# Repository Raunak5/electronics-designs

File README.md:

# KiCad Projects

This repository contains my KiCad practice projects and electronic circuit designs.

Projects:

- Transformerless Power Supply
- AC to DC Converter
- Simple Voltage Regulator

Tools Used:

- KiCad
- Git
- GitHub

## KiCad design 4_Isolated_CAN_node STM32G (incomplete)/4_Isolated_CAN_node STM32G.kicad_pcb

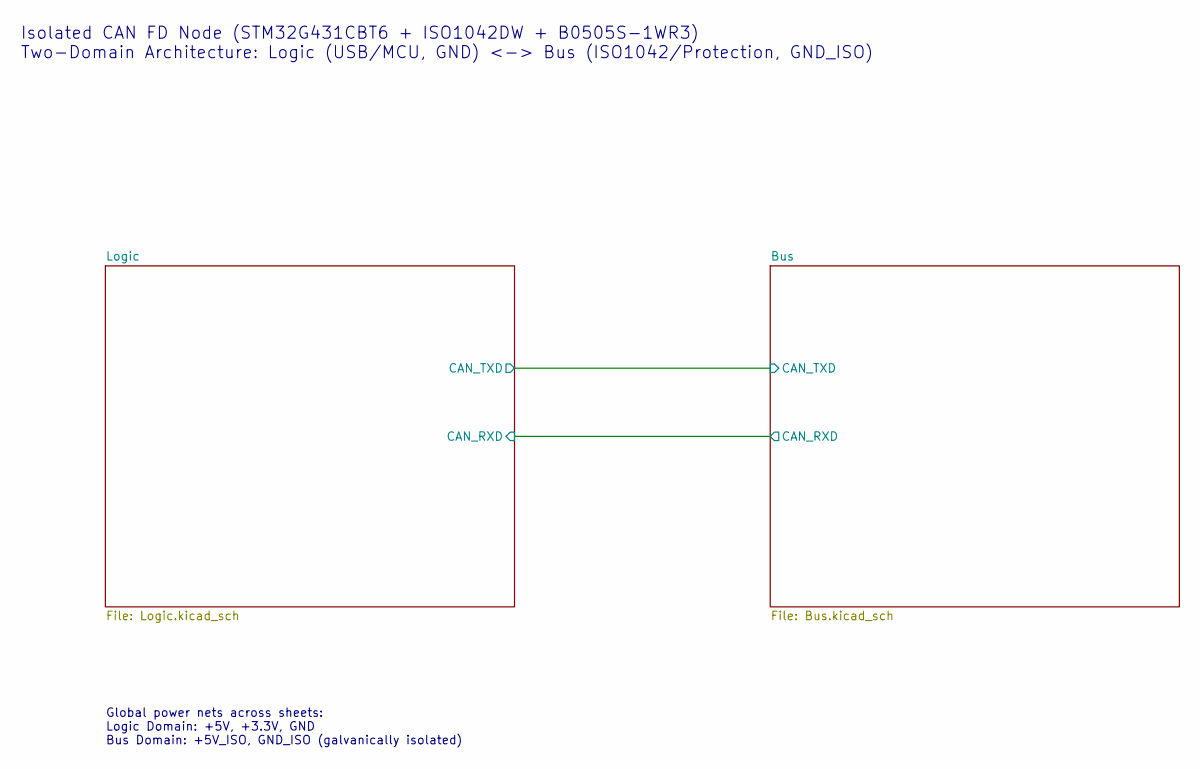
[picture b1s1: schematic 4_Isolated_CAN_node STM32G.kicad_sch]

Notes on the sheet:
Isolated CAN FD Node (STM32G431CBT6 + ISO1042DW + B0505S-1WR3) Two-Domain Architecture: Logic (USB/MCU, GND) <-> Bus (ISO1042/Protection, GND_ISO)
Global power nets across sheets: Logic Domain: +5V, +3.3V, GND Bus Domain: +5V_ISO, GND_ISO (galvanically isolated)

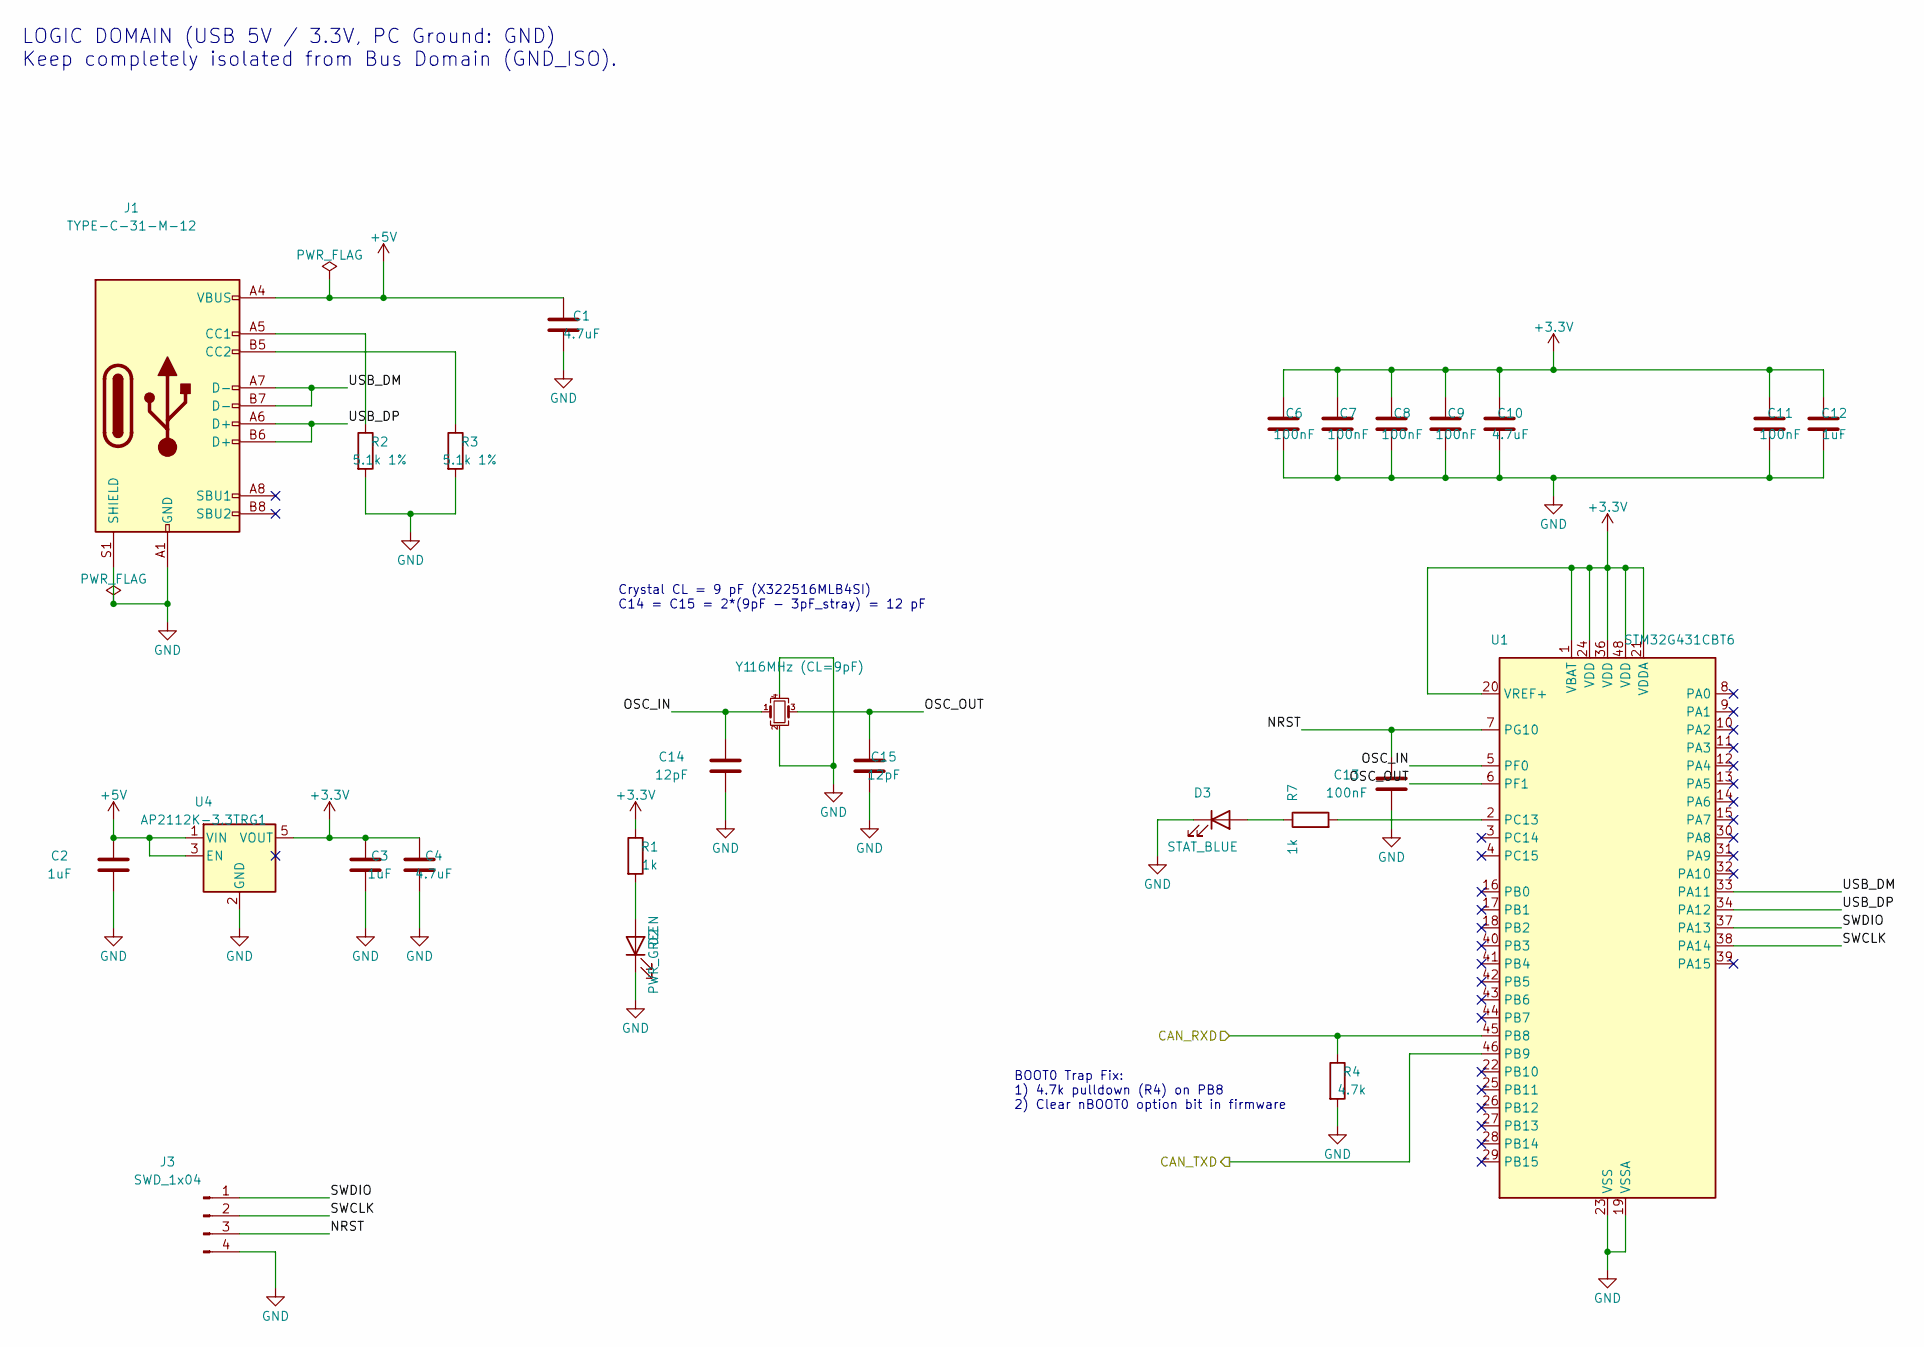
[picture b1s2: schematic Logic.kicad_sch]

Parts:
C1, C4, C10: 4.7uF; C_0603_1608Metric
C2, C3, C12: 1uF; C_0603_1608Metric
C6, C7, C8, C9, C11, C13: 100nF; C_0603_1608Metric
C14, C15: 12pF; C_0603_1608Metric
D2: PWR_GREEN; LED_0603_1608Metric
D3: STAT_BLUE; LED_0603_1608Metric
J1: TYPE-C-31-M-12; USB_C_Receptacle_HRO_TYPE-C-31-M-12; LCSC C165948
J3: SWD_1x04; PinHeader_1x04_P2.54mm_Vertical
R1, R7: 1k; R_0603_1608Metric
R2, R3: 5.1k 1%; R_0603_1608Metric
R4: 4.7k; R_0603_1608Metric
U1: STM32G431CBT6; LQFP-48_7x7mm_P0.5mm
U4: AP2112K-3.3TRG1; SOT-23-5; LCSC C51118
Y1: 16MHz (CL=9pF); Crystal_SMD_3225-4Pin_3.2x2.5mm; LCSC C13738

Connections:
+3.3V: C3.1, C4.1, C6.1, C7.1, C8.1, C9.1, C10.1, C11.1, C12.1, R1.1, U1.1 (VBAT), U1.20 (VREF+), U1.21 (VDDA), U1.24 (VDD), U1.36 (VDD), U1.48 (VDD), U4.5 (VOUT); also elsewhere on the board
+5V: C1.1, C2.1, J1.A4 (VBUS), J1.A9 (VBUS), J1.B4 (VBUS), J1.B9 (VBUS), U4.1 (VIN), U4.3 (EN); also elsewhere on the board
/Bus/CAN_RXD: R4.1, U1.45 (PB8); also elsewhere on the board
/Bus/CAN_TXD: U1.46 (PB9); also elsewhere on the board
/Logic/NRST: C13.1, J3.3, U1.7 (PG10)
/Logic/OSC_IN: C14.1, U1.5 (PF0), Y1.1
/Logic/OSC_OUT: C15.1, U1.6 (PF1), Y1.3
/Logic/SWCLK: J3.2, U1.38 (PA14)
/Logic/SWDIO: J3.1, U1.37 (PA13)
/Logic/USB_DM: J1.A7 (D-), J1.B7 (D-), U1.33 (PA11)
/Logic/USB_DP: J1.A6 (D+), J1.B6 (D+), U1.34 (PA12)
GND: C1.2, C2.2, C3.2, C4.2, C6.2, C7.2, C8.2, C9.2, C10.2, C11.2, C12.2, C13.2, C14.2, C15.2, D2.1 (K), D3.1 (K), J1.A1 (GND), J1.A12 (GND), J1.B1 (GND), J1.B12 (GND), J1.S1 (SHIELD), J3.4, R2.2, R3.2, R4.2, U1.19 (VSSA), U1.23 (VSS), U1.35 (VSS), U1.47 (VSS), U4.2 (GND), Y1.2, Y1.4; also elsewhere on the board
unnamed: D2.2 (A), R1.2
unnamed: D3.2 (A), R7.1
unnamed: J1.A5 (CC1), R2.1
unnamed: J1.B5 (CC2), R3.1
unnamed: R7.2, U1.2 (PC13)

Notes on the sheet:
LOGIC DOMAIN (USB 5V / 3.3V, PC Ground: GND) Keep completely isolated from Bus Domain (GND_ISO).
Crystal CL = 9 pF (X322516MLB4SI) C14 = C15 = 2*(9pF - 3pF_stray) = 12 pF
BOOT0 Trap Fix: 1) 4.7k pulldown (R4) on PB8 2) Clear nBOOT0 option bit in firmware

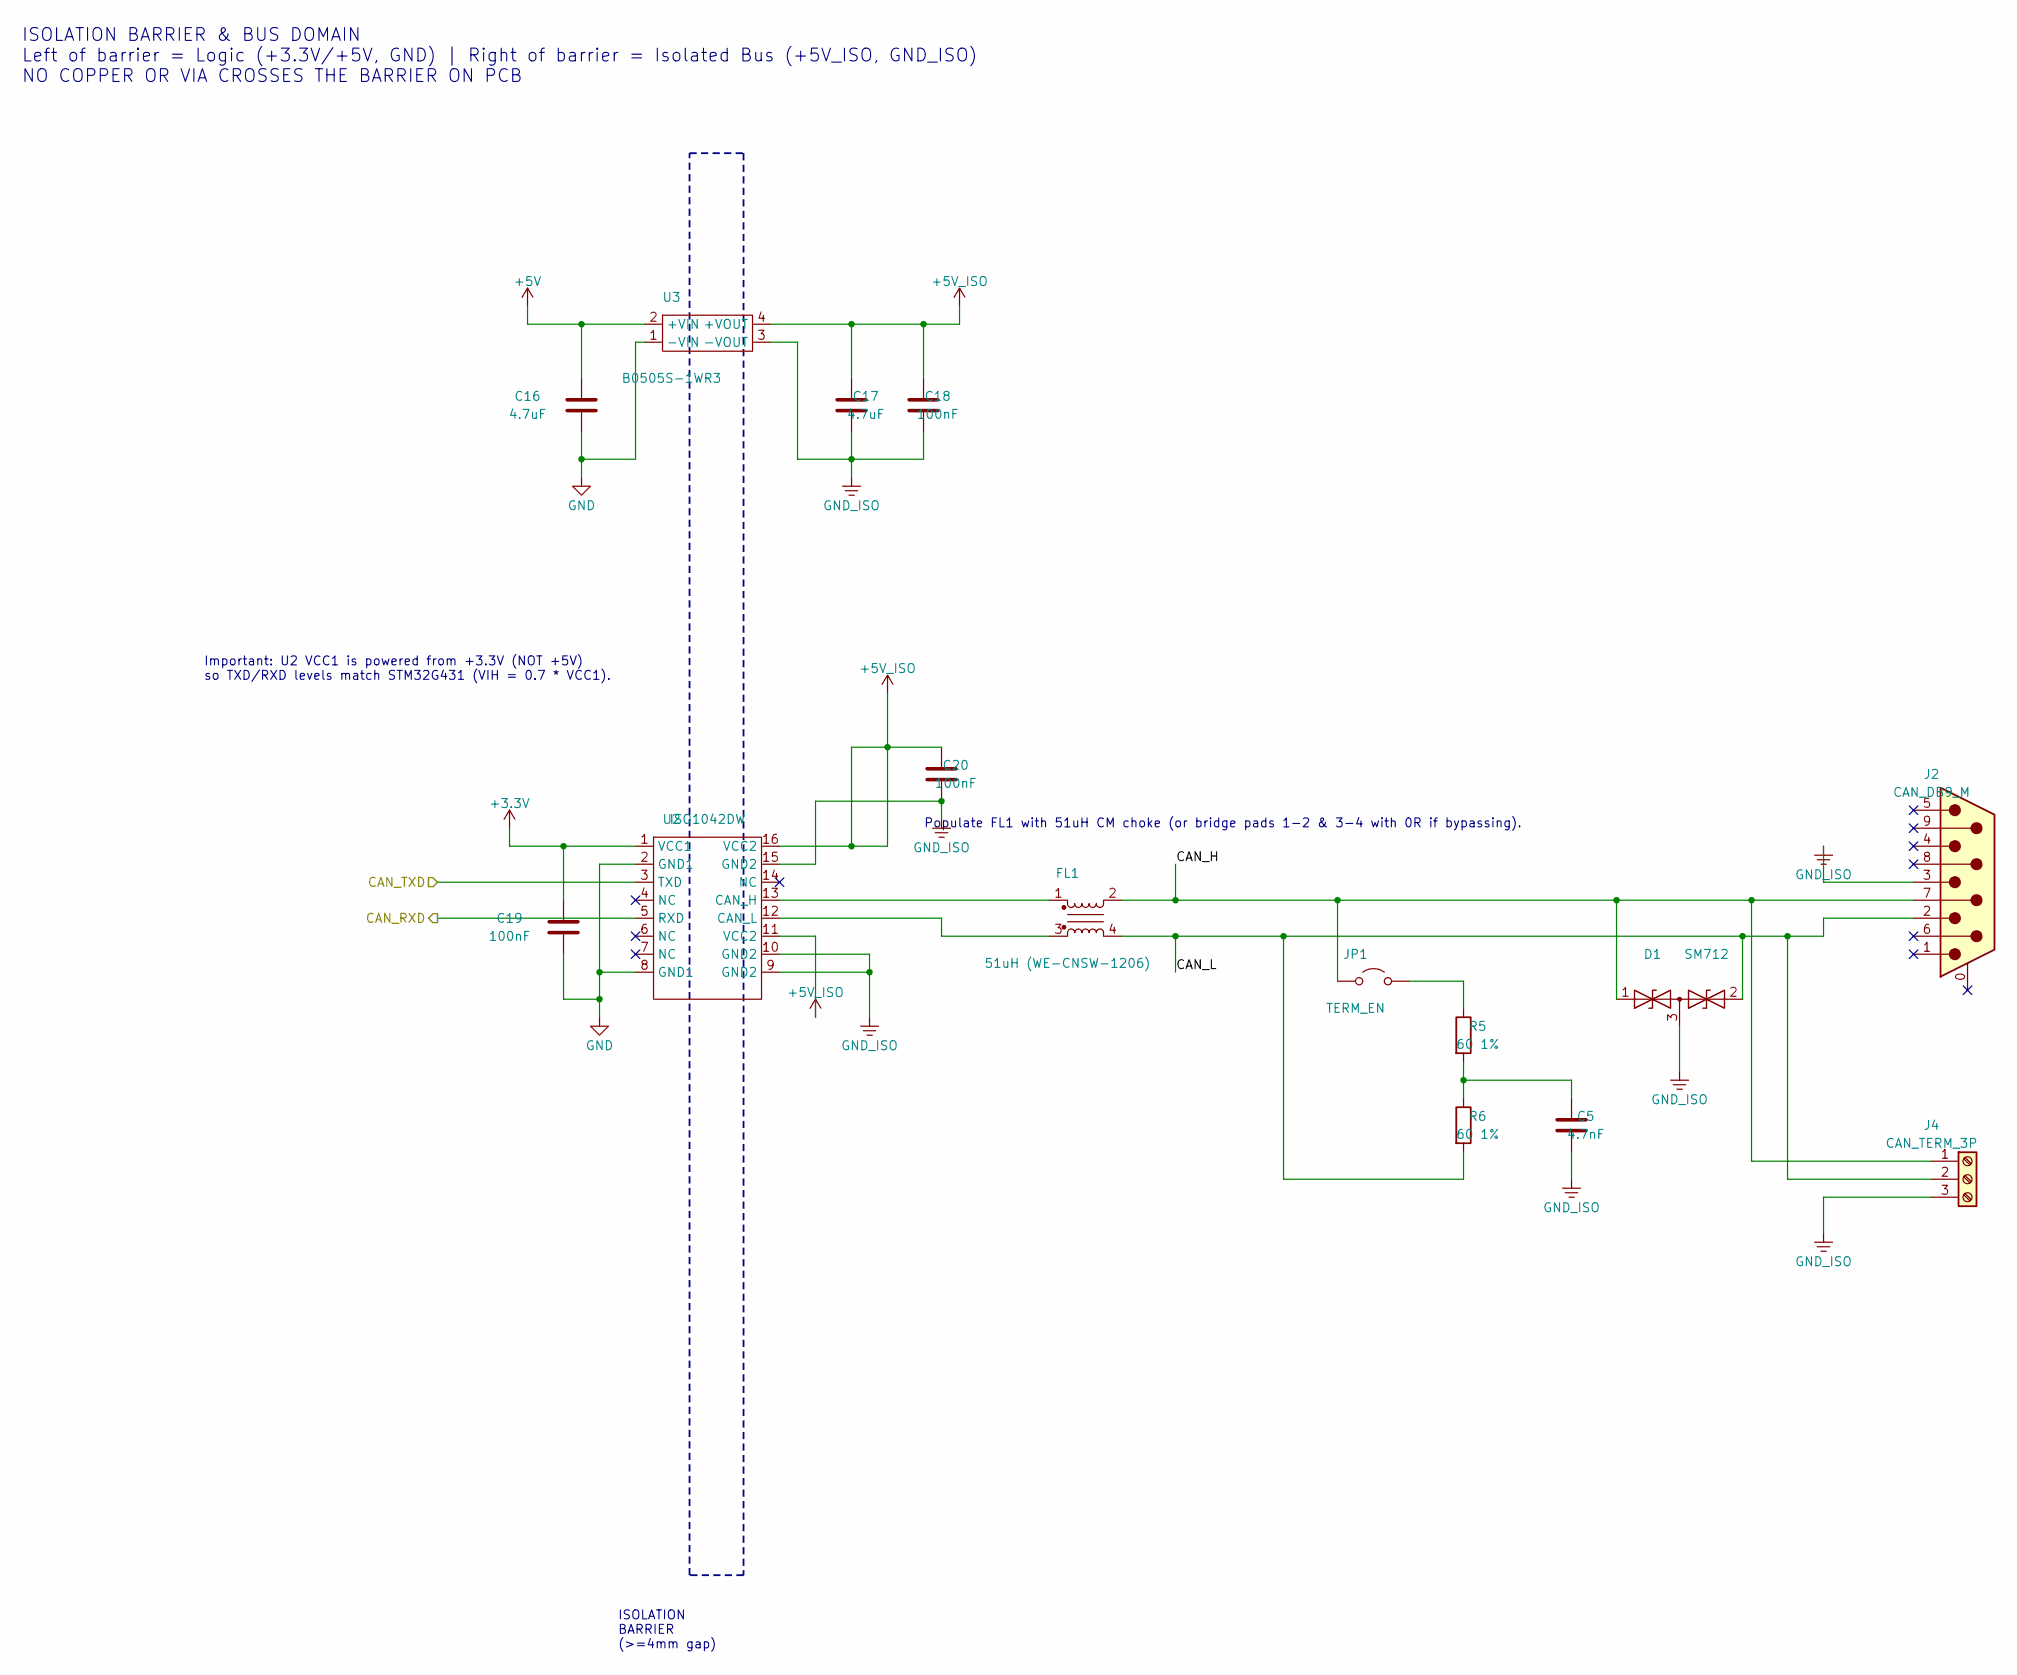
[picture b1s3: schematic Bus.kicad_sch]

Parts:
C5: 4.7nF; C_0603_1608Metric
C16, C17: 4.7uF; C_0603_1608Metric
C18, C19, C20: 100nF; C_0603_1608Metric
D1: SM712; SOT-23; LCSC C404012
FL1: 51uH (WE-CNSW-1206); L_CommonMode_Wurth_WE-CNSW-1206
J2: CAN_DB9_M; DSUB-9_Pins_Horizontal_P2.77x2.84mm_EdgePinOffset7.70mm_Hou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
J4: CAN_TERM_3P; TerminalBlock_Phoenix_MKDS-1,5-3-5.08_1x03_P5.08mm_Horizont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
JP1: TERM_EN; PinHeader_1x02_P2.54mm_Vertical
R5, R6: 60 1%; R_0603_1608Metric
U2: ISO1042DW; SOIC-16W_7.5x10.3mm_P1.27mm; LCSC C1848126
U3: B0505S-1WR3; Converter_DCDC_Murata_MEE1SxxxxSC_THT; LCSC C84643

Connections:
+3.3V: C19.1, U2.1 (VCC1); also elsewhere on the board
+5V: C16.1, U3.2 (+VIN); also elsewhere on the board
+5V_ISO: C17.1, C18.1, C20.1, U2.11 (VCC2), U2.16 (VCC2), U3.4 (+VOUT)
/Bus/CAN_H: D1.1 (A1), FL1.2, J2.7, J4.1, JP1.1 (A)
/Bus/CAN_L: D1.2 (A2), FL1.4, J2.2, J4.2, R6.2
/Bus/CAN_RXD: U2.5 (RXD); also elsewhere on the board
/Bus/CAN_TXD: U2.3 (TXD); also elsewhere on the board
GND: C16.2, C19.2, U2.2 (GND1), U2.8 (GND1), U3.1 (-VIN); also elsewhere on the board
GND_ISO: C5.2, C17.2, C18.2, C20.2, D1.3 (common), J2.3, J4.3, U2.9 (GND2), U2.10 (GND2), U2.15 (GND2), U3.3 (-VOUT)
unnamed: C5.1, R5.2, R6.1
unnamed: JP1.2 (B), R5.1
unnamed: FL1.1, U2.13 (CAN_H)
unnamed: FL1.3, U2.12 (CAN_L)

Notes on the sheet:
ISOLATION BARRIER & BUS DOMAIN Left of barrier = Logic (+3.3V/+5V, GND) | Right of barrier = Isolated Bus (+5V_ISO, GND_ISO) NO COPPER OR VIA CROSSES THE BARRIER ON PCB
ISOLATION BARRIER (>=4mm gap)
Important: U2 VCC1 is powered from +3.3V (NOT +5V) so TXD/RXD levels match STM32G431 (VIH = 0.7 * VCC1).
Populate FL1 with 51uH CM choke (or bridge pads 1-2 & 3-4 with 0R if bypassing).

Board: 2 copper layers, 41 parts (0 on the bottom side), 25 nets, no tracks yet.

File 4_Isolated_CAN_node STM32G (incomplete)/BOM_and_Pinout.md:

# Isolated CAN FD Node — Parts List (Phase 01) & Pinout Reference (Phase 02)

## Phase 01 — Locked BOM & LCSC Reference

> **Important Corrections Applied**
> - **U2 (`ISO1042DW` vs `ISO1042DWV`):** Your 16-pin wide-body SOIC footprint (`SOIC-16W_7.5x10.3mm_P1.27mm`) corresponds to TI's **16-pin `ISO1042DW` / `ISO1042DWR`**, not `ISO1042DWV` (which is an 8-pin wide-body SOIC). The schematic symbol and BOM use `ISO1042DW`.
> - **U2 Logic-Side Supply (`VCC1`):** `ISO1042` `VCC1` is wired to **`+3.3V`** (not `+5V`) because `VIH(min) = 0.7 × VCC1` (`2.31 V` at `3.3 V` vs `3.5 V` at `5 V`), matching the `3.3 V` STM32G431 I/O levels.
> - **Crystal Load Caps (`Y1`):** `X322516MLB4SI` (`C13738`) specifies `CL = 9 pF`. Assuming ~3 pF stray PCB/pin capacitance, `C14 = C15 = 2 × (9 pF − 3 pF) = 12 pF` (C0G/NP0).

| Ref | Part / Value | Package / Footprint | Verified LCSC / MPN Note | Qty (+Spares) |
| :--- | :--- | :--- | :--- | :--- |
| `U1` | `STM32G431CBT6` | `LQFP-48_7x7mm_P0.5mm` | ST `STM32G431CBT6` (check LCSC stock at order time) | 1 (+2 spares) |
| `U2` | `ISO1042DW` | `SOIC-16W_7.5x10.3mm_P1.27mm` | TI `ISO1042DWR` (`C1848126`) | 1 (+2 spares) |
| `U3` | `B0505S-1WR3` | `Converter_DCDC_Murata_MEE1SxxxxSC_THT` (SIP-4) | Mornsun `B0505S-1WR3` (`C84643` / alt `C2992394`) | 1 (+2 spares) |
| `U4` | `AP2112K-3.3TRG1` | `SOT-23-5` | Diodes Inc `AP2112K-3.3TRG1` (`C51118`) | 1 (+2 spares) |
| `Y1` | `16 MHz` crystal (`CL = 9 pF`) | `Crystal_SMD_3225-4Pin_3.2x2.5mm` | YXC `X322516MLB4SI` (`C13738`) | 1 (+2 spares) |
| `D1` | `SM712` (+12 V / −7 V TVS) | `SOT-23` | Bourns `CDSOT23-SM712` (`C404012`) | 1 (+2 spares) |
| `FL1` | `51 µH` CM choke (or `0 Ω` bypass) | `L_CommonMode_Wurth_WE-CNSW-1206` (1206-4) | Populate 1206-4 CAN CM choke later or bridge `1-2` & `3-4` with `0 Ω` | 1 |
| `J1` | USB-C 16-pin receptacle | `USB_C_Receptacle_HRO_TYPE-C-31-M-12` | HRO `TYPE-C-31-M-12` (`C165948`) | 1 |
| `J2` | DB9 male THT | `DSUB-9_Pins_Horizontal_P2.77x2.84mm_EdgePinOffset7.70mm_Housed_MountingHolesOffset9.12mm` | Standard right-angle PCB DE9 male | 1 |
| `J4` | 3-pin screw terminal (5.08 mm) | `TerminalBlock_Phoenix_MKDS-1,5-3-5.08_1x03_P5.08mm_Horizontal` | 3-pin 5.08 mm THT terminal block | 1 |
| `J3` | 4-pin SWD header | `PinHeader_1x04_P2.54mm_Vertical` | 1×4 2.54 mm header (`SWDIO`, `SWCLK`, `NRST`, `GND`) | 1 |
| `JP1` | 2-pin termination jumper | `PinHeader_1x02_P2.54mm_Vertical` | 1×2 2.54 mm header + shunt | 1 |
| `D2`, `D3` | Indicator LEDs (Power, Status) | `LED_0603_1608Metric` | Green (`D2`), Blue (`D3`) 0603 LEDs | 2 |
| `R1`, `R7` | `1 kΩ` (LED current limit) | `R_0603_1608Metric` | 0603 5% or 1% | 2 |
| `R2`, `R3` | `5.1 kΩ` 1% (USB-C CC1/CC2) | `R_0603_1608Metric` | 0603 1% | 2 |
| `R4` | `4.7 kΩ` (PB8/BOOT0 pulldown) | `R_0603_1608Metric` | 0603 1% or 5% | 1 |
| `R5`, `R6` | `60 Ω` 1% (split termination) | `R_0603_1608Metric` | 0603 1% (or `60.4 Ω` 1% E96 standard) | 2 |
| `C5` | `4.7 nF` (split termination) | `C_0603_1608Metric` | 0603 ≥50 V X7R/C0G | 1 |
| `C14`, `C15` | `12 pF` (HSE crystal load) | `C_0603_1608Metric` | 0603 C0G/NP0 50 V | 2 |
| `C6–C9, C11, C13, C18–C20` | `100 nF` (decoupling + NRST) | `C_0603_1608Metric` | 0603 X7R/X5R ≥16 V | 9 |
| `C2, C3, C12` | `1 µF` (LDO + VDDA) | `C_0603_1608Metric` | 0603 X5R/X7R ≥10 V | 3 |
| `C1, C4, C10, C16, C17` | `4.7 µF` (bulk decoupling) | `C_0603_1608Metric` | 0603 X5R/X7R ≥10 V | 5 |

---

## Phase 02 — STM32G431CBT6 Pinout & CubeMX Configuration

### CubeMX Setup Order
1. **SYS → Debug:** `Serial Wire` (`PA13` = `SWDIO`, `PA14` = `SWCLK`)
2. **RCC → HSE:** `Crystal/Ceramic Resonator` (`PF0` = `RCC_OSC_IN`, `PF1` = `RCC_OSC_OUT`, 16 MHz)
3. **USB → Device (FS):** Enabled (`PA11` = `USB_DM`, `PA12` = `USB_DP`)
4. **FDCAN1 → Mode:** `Classic + FD`, remapped off `PA11/PA12` onto **`PB8` (`FDCAN1_RX`)** and **`PB9` (`FDCAN1_TX`)**
5. **GPIO Output:** `PC13` = `LED_STATUS`
6. **Clock Tree:** 16 MHz HSE → PLL → `SYSCLK` (up to 170 MHz), **`48 MHz` USB clock** (via PLLQ or HSI48+CRS; use PLL from 16 MHz HSE for deterministic timing)
7. **Option Bytes (Critical for `PB8/BOOT0` trap):** Clear `nBOOT0` / `nSWBOOT0` (set `nSWBOOT0 = 0`, `nBOOT0 = 1` in STM32CubeProgrammer so MCU boots from main Flash regardless of `PB8` state; `R4` `4.7 kΩ` pulldown protects the pre-option-byte reset window).

### Pin Assignment Table (`U1: STM32G431CBT6`)

| Pin # | Pin Name | Schematic Net | Function |
| :--- | :--- | :--- | :--- |
| `1` | `VBAT` | `+3.3V` | Tied to 3.3 V + `100 nF` (`C6`) |
| `2` | `PC13` | `LED_STATUS` (via `R7`/`D3`) | Firmware status LED |
| `5` | `PF0` | `/Logic/OSC_IN` | 16 MHz HSE crystal (`Y1.1`, `C14` `12 pF`) |
| `6` | `PF1` | `/Logic/OSC_OUT` | 16 MHz HSE crystal (`Y1.3`, `C15` `12 pF`) |
| `7` | `PG10` | `/Logic/NRST` | Reset (`C13` `100 nF` to `GND`, `J3.3`) |
| `19` | `VSSA` | `GND` | Analog ground |
| `20` | `VREF+` | `+3.3V` | Analog reference (`C11`, `C12`) |
| `21` | `VDDA` | `+3.3V` | Analog power |
| `23, 35, 47` | `VSS` | `GND` | Logic ground |
| `24, 36, 48` | `VDD` | `+3.3V` | Logic power (`C7–C10`) |
| `33` | `PA11` | `/Logic/USB_DM` | USB FS D− (`J1.A7/B7`) |
| `34` | `PA12` | `/Logic/USB_DP` | USB FS D+ (`J1.A6/B6`) |
| `37` | `PA13` | `/Logic/SWDIO` | SWD data (`J3.1`) |
| `38` | `PA14` | `/Logic/SWCLK` | SWD clock (`J3.2`) |
| `45` | `PB8` | `/Bus/CAN_RXD` | `FDCAN1_RX` + `4.7 kΩ` (`R4`) to `GND` (`U2.RXD`) |
| `46` | `PB9` | `/Bus/CAN_TXD` | `FDCAN1_TX` (`U2.TXD`) |

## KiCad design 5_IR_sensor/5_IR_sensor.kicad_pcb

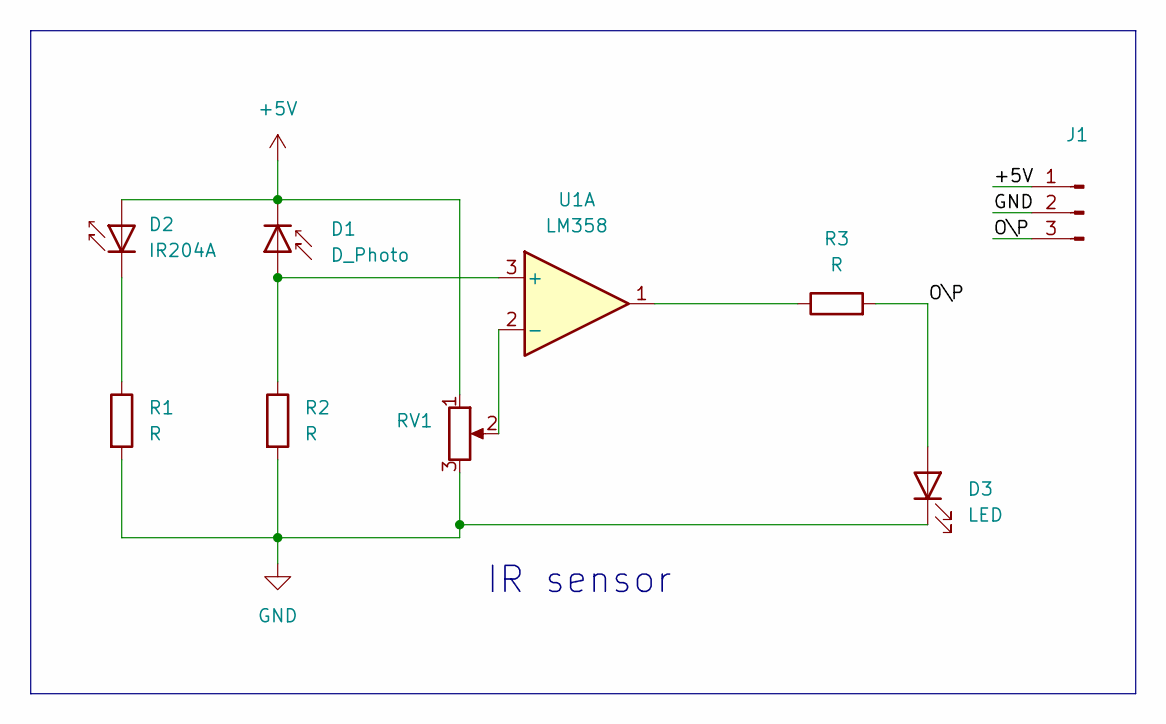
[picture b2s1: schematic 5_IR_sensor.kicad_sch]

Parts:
D1: D_Photo; LED_1W_3W_R8
D2: IR204A; LED_1W_3W_R8
D3: LED; LED_1W_3W_R8
J1: joint; PinHeader_1x03_P2.54mm_Vertical
R1, R2, R3: R; R_0805_2012Metric
RV1: R_Potentiometer; Potentiometer_ACP_CA9-VSMD_Vertical
U1: LM358; SOIC-8-1EP_3.9x4.9mm_P1.27mm_EP2.514x3.2mm_ThermalVias

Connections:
+5V: D1.1 (K), D2.2 (A), J1.1, RV1.1
/O\P: D3.2 (A), J1.3, R3.2
GND: D3.1 (K), J1.2, R1.2, R2.2, RV1.3
unnamed: D1.2 (A), R2.1, U1.3 (+)
unnamed: D2.1 (K), R1.1
unnamed: R3.1, U1.1
unnamed: RV1.2, U1.2 (-)

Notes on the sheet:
IR sensor

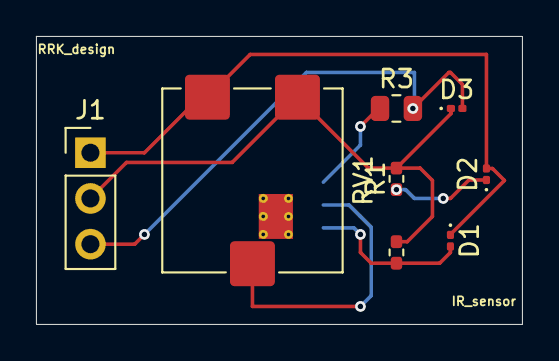
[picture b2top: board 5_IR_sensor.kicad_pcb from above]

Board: 2 copper layers, 27.0 x 16.0 mm, 9 parts (1 on the bottom side), 7 nets.

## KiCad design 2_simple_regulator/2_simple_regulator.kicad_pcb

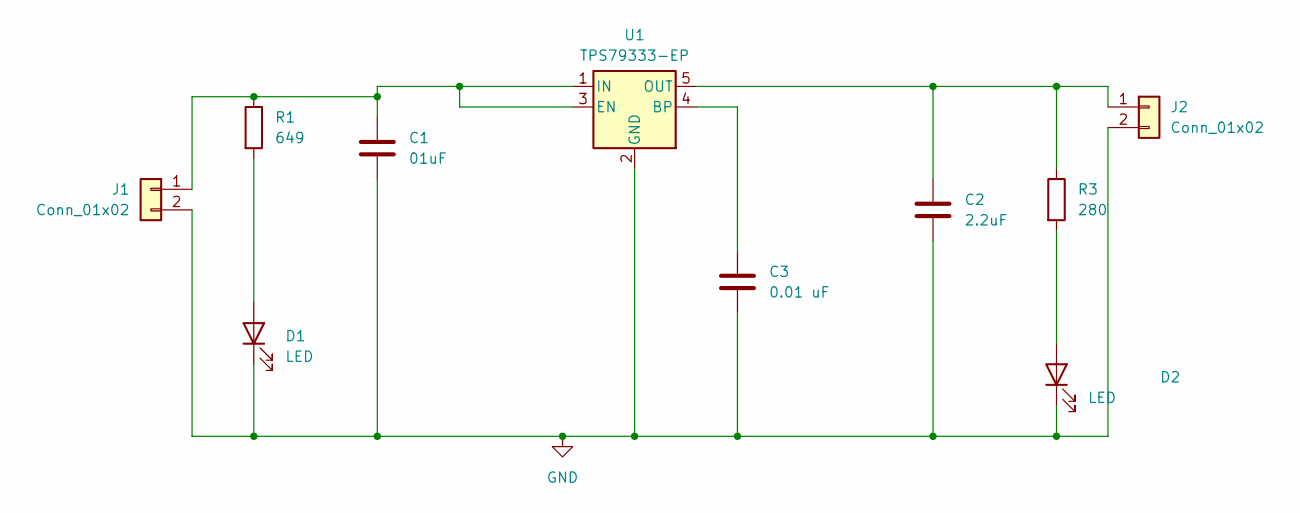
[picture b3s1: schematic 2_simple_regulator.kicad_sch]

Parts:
C1: 01uF; C_0805_2012Metric
C2: 2.2uF; C_0805_2012Metric
C3: 0.01 uF; C_0805_2012Metric
D1, D2: LED; LED_0805_2012Metric
J1, J2: Conn_01x02; PinHeader_1x02_P2.54mm_Vertical
R1: 649; R_0805_2012Metric
R3: 280; R_0805_2012Metric
U1: TPS79333-EP; SOT-23-5

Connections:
GND: C1.2, C2.2, C3.2, D1.1 (K), D2.1 (K), J1.2, J2.2, U1.2 (GND)
unnamed: D1.2 (A), R1.2
unnamed: D2.2 (A), R3.2
unnamed: C1.1, J1.1, R1.1, U1.1 (IN), U1.3 (EN)
unnamed: C2.1, J2.1, R3.1, U1.5 (OUT)
unnamed: C3.1, U1.4 (BP)

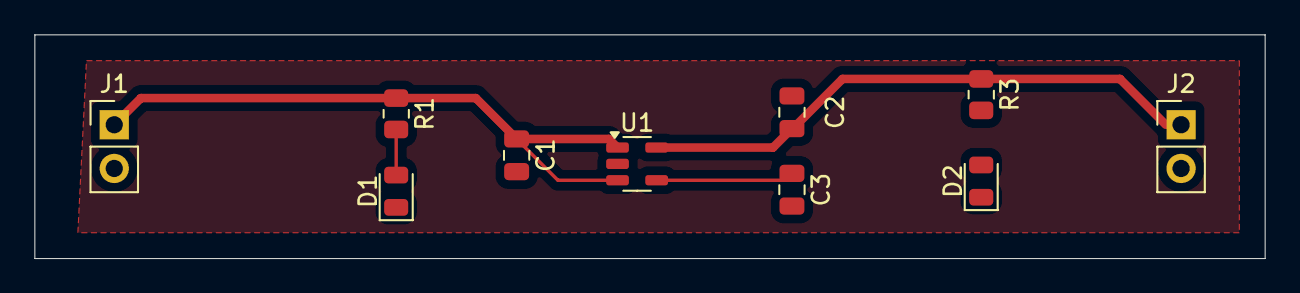
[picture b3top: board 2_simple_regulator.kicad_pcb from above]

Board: 2 copper layers, 71.5 x 13.0 mm, 10 parts (0 on the bottom side), 6 nets.

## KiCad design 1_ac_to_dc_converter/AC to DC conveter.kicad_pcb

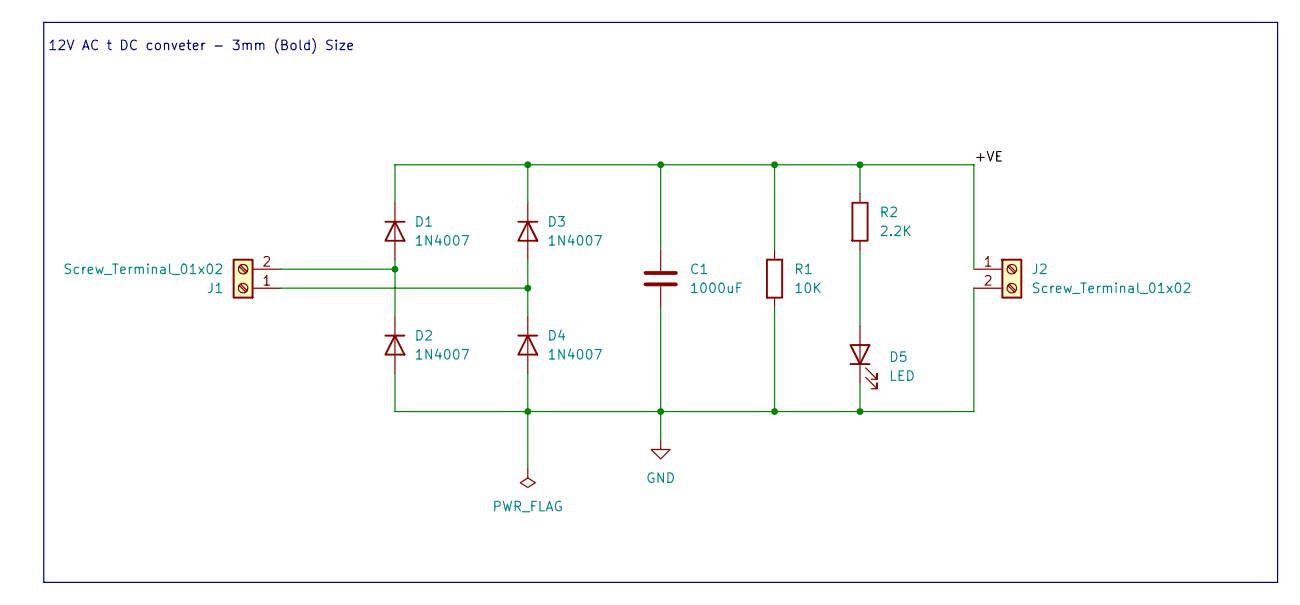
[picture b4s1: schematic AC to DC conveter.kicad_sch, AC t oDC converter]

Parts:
C1: 1000uF; CP_Radial_D8.0mm_P3.50mm
D1, D2, D3, D4: 1N4007; D_DO-41_SOD81_P10.16mm_Horizontal
D5: LED; LED_D5.0mm
J1, J2: Screw_Terminal_01x02; TerminalBlock_Altech_AK300-2_P5.00mm
R1: 10K; R_Axial_DIN0204_L3.6mm_D1.6mm_P7.62mm_Horizontal
R2: 2.2K; R_Axial_DIN0204_L3.6mm_D1.6mm_P7.62mm_Horizontal

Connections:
/+VE: C1.1, D1.1 (K), D3.1 (K), J2.1, R1.1, R2.1
GND: C1.2, D2.2 (A), D4.2 (A), D5.1 (K), J2.2, R1.2
unnamed: D1.2 (A), D2.1 (K), J1.2
unnamed: D3.2 (A), D4.1 (K), J1.1
unnamed: D5.2 (A), R2.2

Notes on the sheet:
12V AC t DC conveter - 3mm (Bold) Size

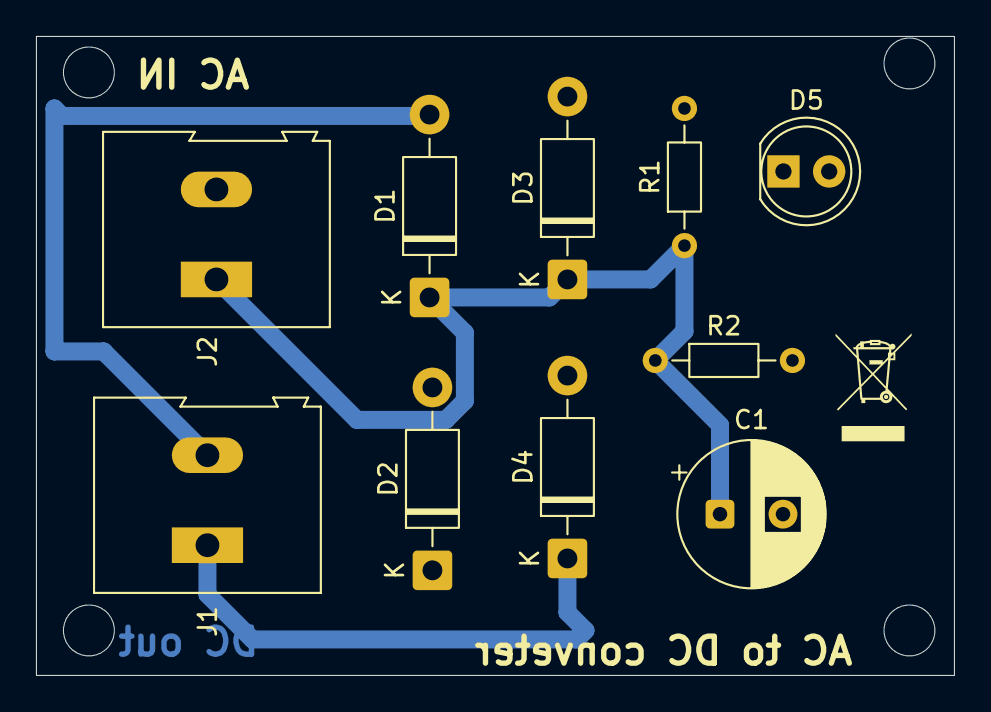
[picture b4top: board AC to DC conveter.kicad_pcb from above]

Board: 2 copper layers, 51.0 x 35.5 mm, 10 parts (0 on the bottom side), 5 nets.

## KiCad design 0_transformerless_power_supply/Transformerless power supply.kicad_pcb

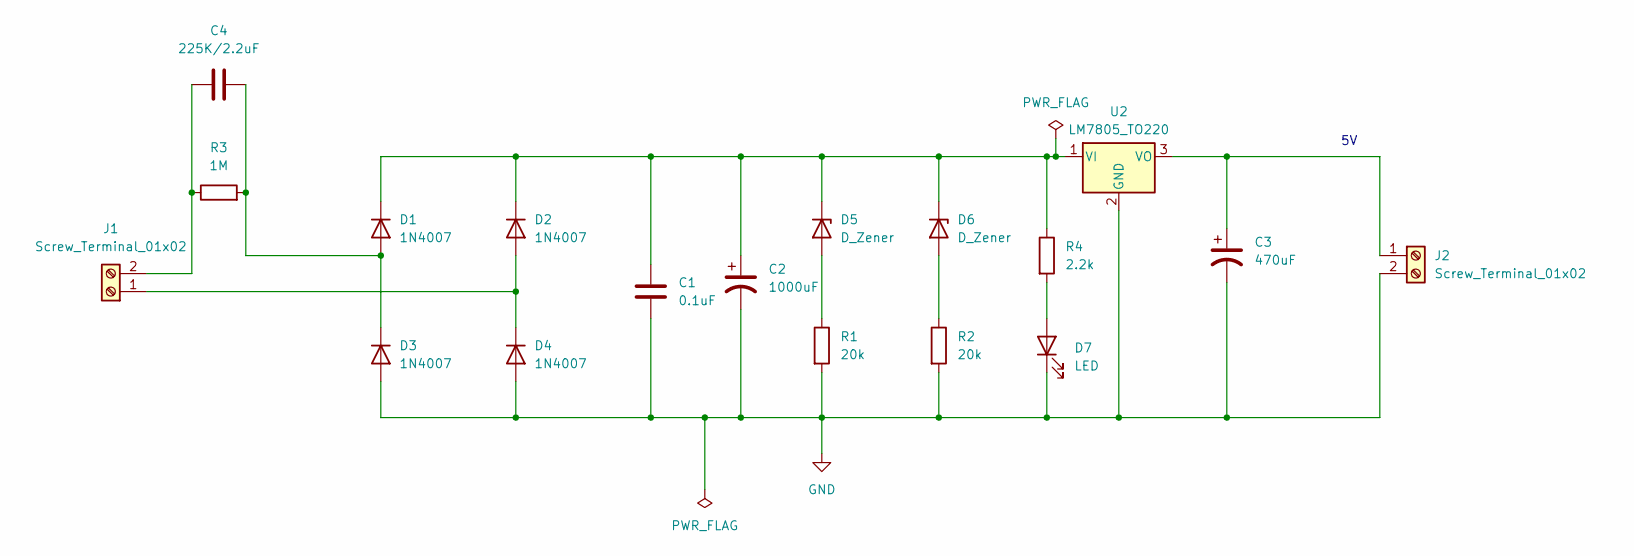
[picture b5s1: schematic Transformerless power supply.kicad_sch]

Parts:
C1: 0.1uF; C_Disc_D4.7mm_W2.5mm_P5.00mm
C2: 1000uF; CP_Radial_D10.0mm_P5.00mm
C3: 470uF; CP_Radial_D10.0mm_P3.80mm
C4: 225K/2.2uF; C_Rect_L18.0mm_W7.0mm_P15.00mm_FKS3_FKP3
D1, D2, D3, D4: 1N4007; D_DO-41_SOD81_P10.16mm_Horizontal
D5, D6: D_Zener; D_A-405_P7.62mm_Horizontal
D7: LED; LED_D5.0mm
J1, J2: Screw_Terminal_01x02; TerminalBlock_bornier-2_P5.08mm
R1, R2: 20k; R_Axial_DIN0207_L6.3mm_D2.5mm_P7.62mm_Horizontal
R3: 1M; R_Axial_DIN0207_L6.3mm_D2.5mm_P7.62mm_Horizontal
R4: 2.2k; R_Axial_DIN0207_L6.3mm_D2.5mm_P7.62mm_Horizontal
U2: LM7805_TO220; TO-220-3_Vertical

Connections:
GND: C1.2, C2.2, C3.2, D3.2 (A), D4.2 (A), D7.1 (K), J2.2, R1.2, R2.2, U2.2 (GND)
unnamed: C4.2, D1.2 (A), D3.1 (K), R3.2
unnamed: C1.1, C2.1, D1.1 (K), D2.1 (K), D5.1 (K), D6.1 (K), R4.1, U2.1 (VI)
unnamed: D2.2 (A), D4.1 (K), J1.1
unnamed: D5.2 (A), R1.1
unnamed: D6.2 (A), R2.1
unnamed: D7.2 (A), R4.2
unnamed: C4.1, J1.2, R3.1
unnamed: C3.1, J2.1, U2.3 (VO)

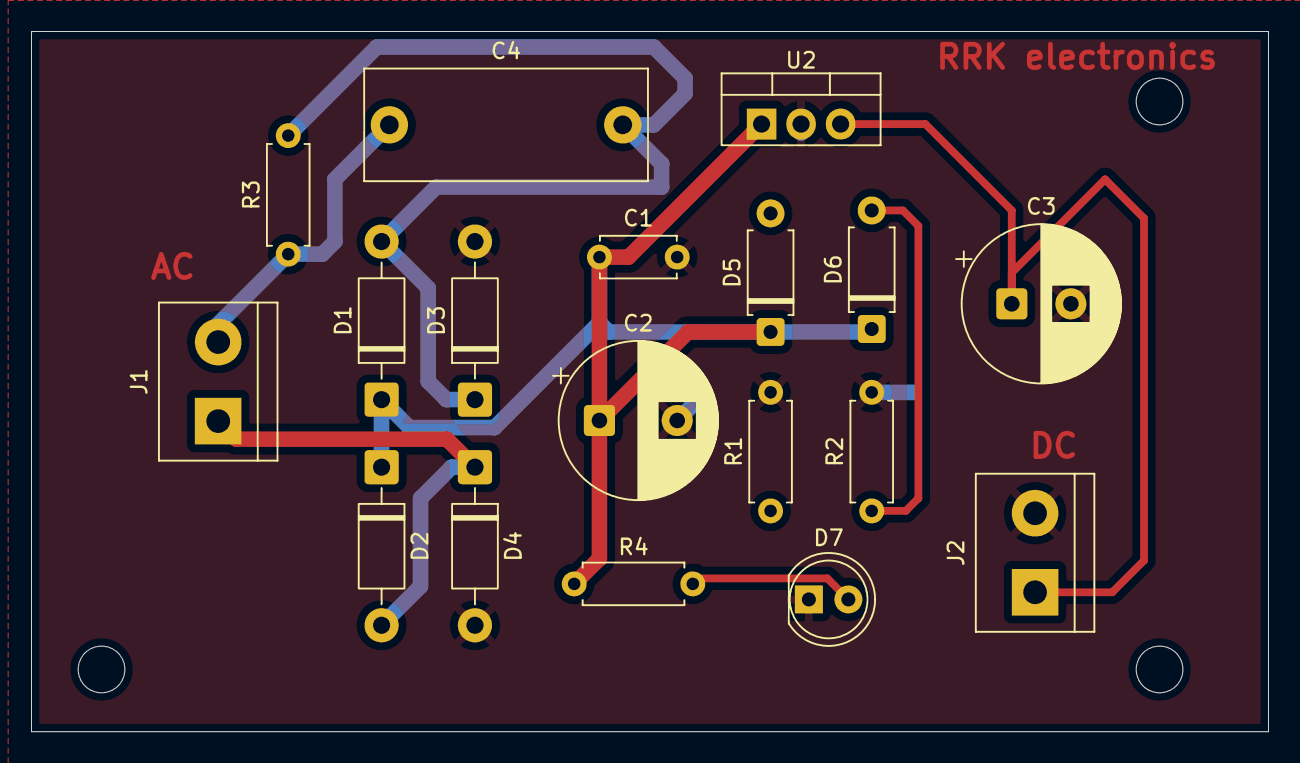
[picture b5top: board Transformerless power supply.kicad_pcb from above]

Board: 2 copper layers, 79.5 x 45.0 mm, 18 parts (0 on the bottom side), 9 nets.

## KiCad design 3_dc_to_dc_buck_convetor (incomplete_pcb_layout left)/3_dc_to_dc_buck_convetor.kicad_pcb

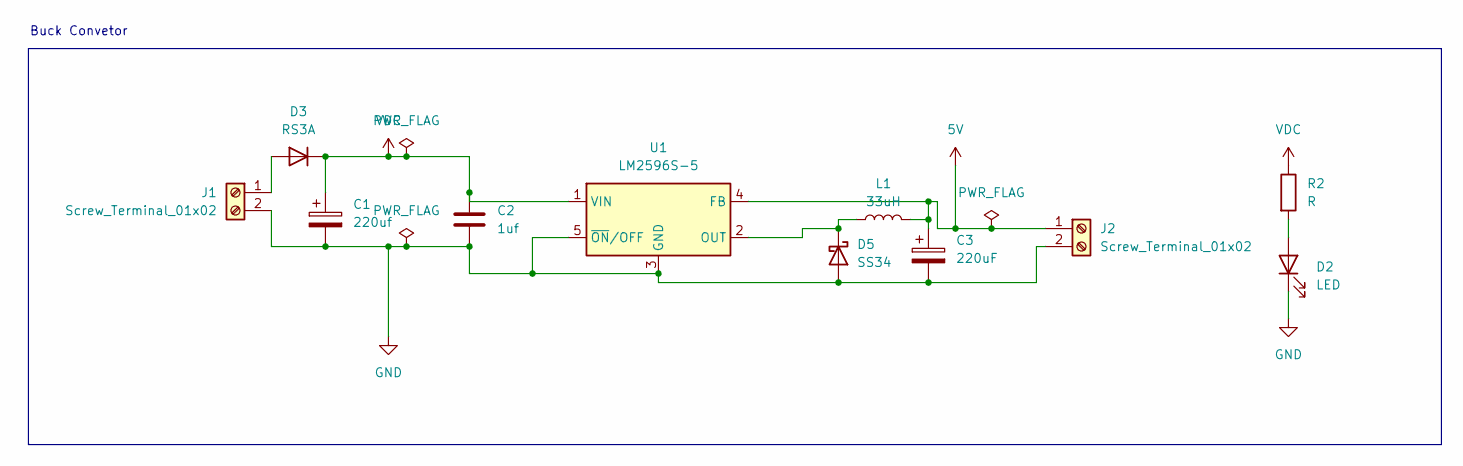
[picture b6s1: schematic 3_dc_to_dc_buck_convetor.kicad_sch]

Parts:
C1: 220uf; CP_Radial_D8.0mm_P3.50mm
C2: 1uf; C_Disc_D3.4mm_W2.1mm_P2.50mm
C3: 220uF; CP_Radial_D8.0mm_P3.50mm
D2: LED; LED_D5.0mm
D3: RS3A; D_SMA
D5: SS34; D_SMA
J1, J2: Screw_Terminal_01x02; TerminalBlock_bornier-2_P5.08mm
L1: 33uH; L_Radial_D10.5mm_P5.00mm_Abacron_AISR-01
R2: R; R_Axial_DIN0207_L6.3mm_D2.5mm_P10.16mm_Horizontal
U1: LM2596S-5; TO-263-5_TabPin3

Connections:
5V: C3.1, J2.1, L1.2, U1.4 (FB)
GND: C1.2, C2.2, C3.2, D2.1 (K), D5.2 (A), J1.2, J2.2, U1.3 (GND), U1.5 (~ON/OFF)
unnamed: D2.2 (A), R2.2
unnamed: D3.2 (A), J1.1
unnamed: D5.1 (K), L1.1, U1.2 (OUT)
VDC: C1.1, C2.1, D3.1 (K), R2.1, U1.1 (VIN)

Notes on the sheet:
Buck Convetor

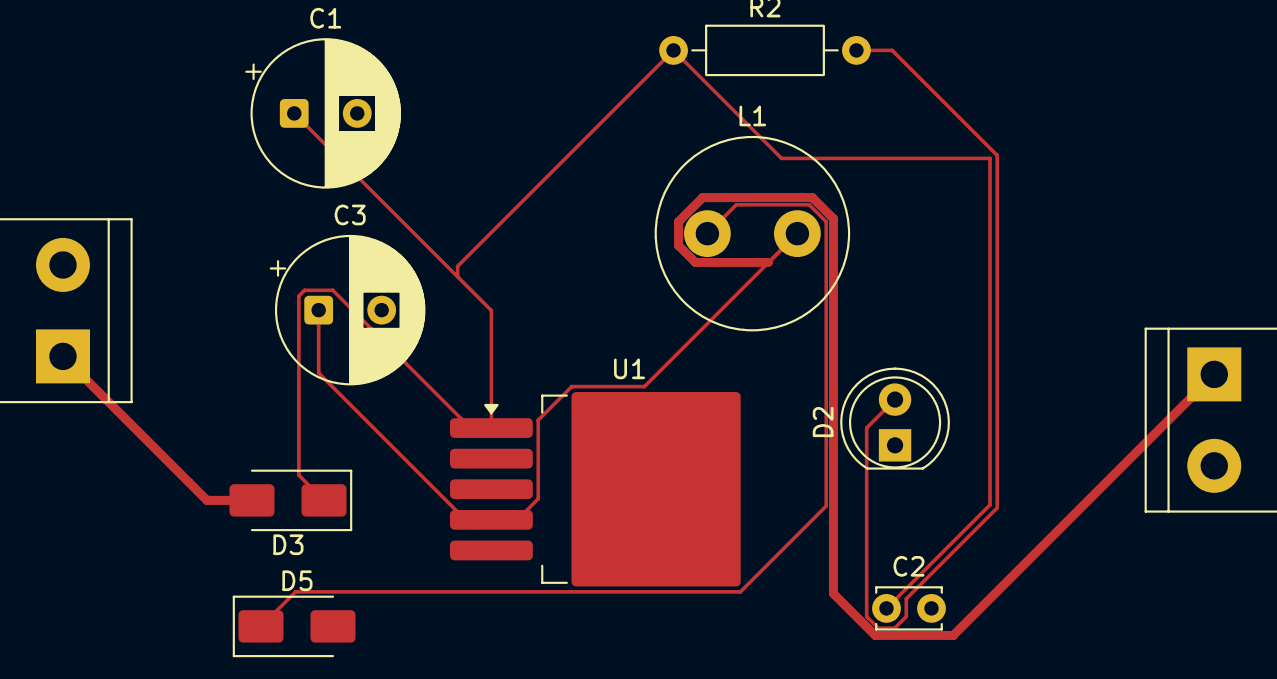
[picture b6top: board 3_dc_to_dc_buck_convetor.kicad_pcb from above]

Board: 2 copper layers, 11 parts (0 on the bottom side), 6 nets.
